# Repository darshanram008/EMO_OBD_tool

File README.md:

# On board diagnostic tool: developed for EMO energy pvt ltd. 
## On Board diagnostic tool is a simple PCB that can be interfaced with the internal battery management system that cannot be accessed during the maintence or diagnostics of the battery pack 

<!--Table  of contents
- [section 1](#section-1)
- [section 2](#section-2)-->

*The priamry functionn of the OBD tool:*
1. Communicate via controller area network (CAN) protocol to the battery and
request the BMS to send necessary data.
2. Communicate via the Universal serial asynchronous RX-TX protocol to the GUI
and deliver the data in human readable from.

*The following operations are implemenetd*
1. Request real time data containing cell voltages, pack voltage, pack current,
temperatures, error and faults from the BMS and transmit to the USB via UART
in the form of strings appended with certain identifiers.
2. Request the configuration parameters from the BMS that was already uploaded
upon getting a command request from the GUI
3. Push the new configuration parameters to the BMS on command request from the
GUI.
4. Request SD card data to be downloaded on request from the GUI.
5. Change baud rates of UART and CAN upon command request from GUI
6. Flow control between OBD and BMS whenever there is an event of exchanging
data.

## 
- Microcontroller unit: Microchip PIC18F27Q84
- CAN transciever: Microchip MCP2551; variable Baud rate upto 1Mbps
- UART to USB converter: Silicon labs CP2102; variable baud rate uptp 115200
- Micrchip MPLAB X IDE

<!-- > some block quote itseems -->

<!-- `this is where code comes` -->

----------------
<!--
[We can post any link if you want] (https://github.com/darshanram008/EMO_OBD_tool/edit/main/README.md)

This is a footnote, you press this it will take you to the footnote. [^1]
Note: Footnotes are always at the end of this file.
## SECTION 1
> This is table

|   Left side     | Right side     |
|-------------|------------|
| 1. The advantage is good | 1. The advantage is bad |
| 2. The advantage is good | 2. The advantage is bad |
| 3. The advantage is good | 3. The advantage is bad |
| 4. The advantage is good | 4. The advantage is bad |

```
{
   \\This is fenced code 
  if (count == 0)
  {
  printf("Hello, zeros"):  
  }

}
```
## SECTION 2
> Definitions

UART
: Universal Asyncronous receiver and transmitter

CAN
: Controller area network

~~Strikeout anything~~

- [x] Task completed
- [x] Task completed
- [ ] Task Incomplete
- [ ] Task incomplete

There are emoji as well! :joy:

i have more :angry:

take more 📶

==Some very important points==.

to put subscript you can do this H<sub>2</sub>O

To put superscript do this X<sup>2</sup>Y

[^1]: This is the footnote, you can add any references you want.

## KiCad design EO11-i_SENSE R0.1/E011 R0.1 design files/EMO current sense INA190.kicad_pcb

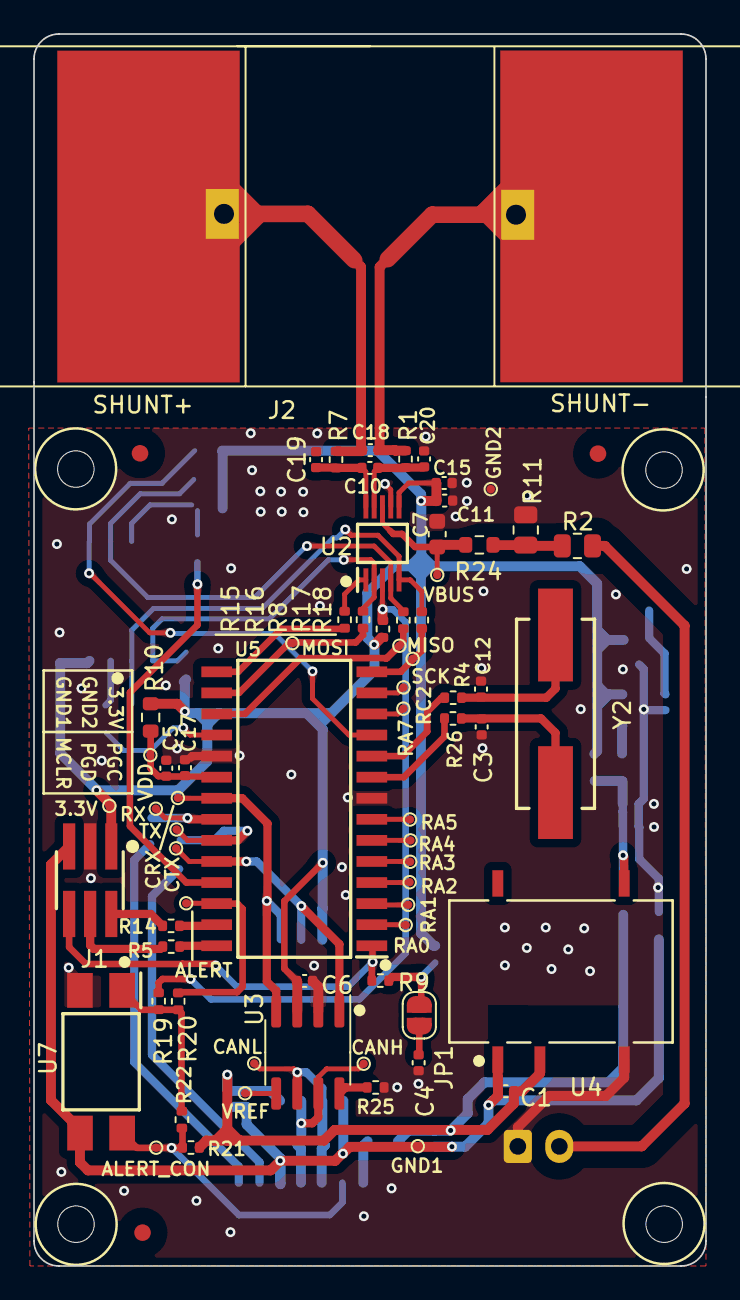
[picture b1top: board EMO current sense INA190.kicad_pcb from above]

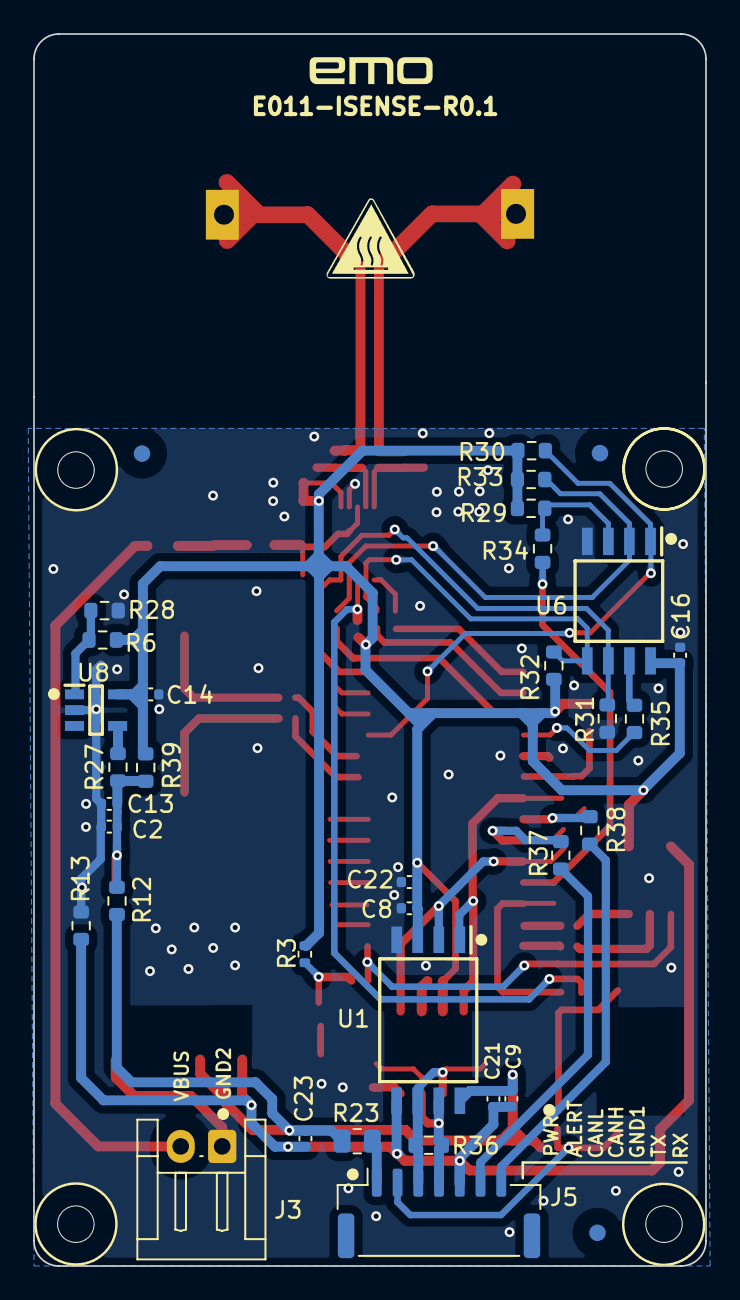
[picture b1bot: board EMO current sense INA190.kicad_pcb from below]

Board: 2 copper layers, 40.5 x 74.2 mm, 111 parts (35 on the bottom side), 62 nets.

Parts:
5V_PIC1: 3.3V; testpoint_0.5mm
C1, C4: 4.7uF; C_0402_1005Metric
C2: 10uF; C_0402_1005Metric
C3, C12: 33pF; C_0402_1005Metric
C5, C11: 100nF; C_0402_1005Metric
C6, C8, C9, C13, C16: 0.1uF; C_0402_1005Metric
C7: 100nF; C_0603_1608Metric
C10, C18, C19, C20, C21, C22: 1uF; C_0402_1005Metric
C14: 0.47uF; C_0402_1005Metric
C15, C17: 0.1nF; C_0402_1005Metric
C23: 47uF; C_0402_1005Metric
FID1, FID2, FID3, FID4, FID5, FID6: Fiducial; fiducial
H1, H2, H3, H4: MountingHole; MountingHole_2.2mm_M2
J1: samtec_03x02; SAMTEC_1.27mm_03x02
J2: current shunt; wsbs8518_shunt
J3: VBUS; JST_EH_S2B-EH_1x02_P2.50mm_Horizontal
J5: Conn_01x07_Pin; JST_GH_SM07B-GHS-TB_1x07-1MP_P1.25mm_Horizontal
JP1: Jumper_Open; SolderJumper-2_P1.3mm_Open_RoundedPad1.0x1.5mm
R1, R5, R7, R14, R25: 10R; R_0402_1005Metric
R2: 10k; R_0805_2012Metric
R3, R8: 10k; R_0402_1005Metric
R4, R15, R16, R17, R18, R19, R20, R21, R22, R26: 1k; R_0402_1005Metric
R6: 18k; R_0603_1608Metric
R9: 470R; R_0402_1005Metric
R10, R12, R13, R27, R37, R38, R39: 0R; R_0603_1608Metric
R11: 1k; R_0805_2012Metric
R23: 0R; R_0805_2012Metric
R24, R29, R30, R31, R32, R33, R34, R35: 1k; R_0603_1608Metric
R28: 10k; R_0603_1608Metric
R36: 120R; R_0603_1608Metric
TP1: ALERT_CON; testpoint_0.5mm
TP2: VBUS; testpoint_0.5mm
TP3: GND1; testpoint_0.5mm
TP4: CANH; testpoint_0.5mm
TP5: CANL; testpoint_0.5mm
TP6: MISO; testpoint_0.5mm
TP7: SCK; testpoint_0.5mm
TP8: MOSI; testpoint_0.5mm
TP9: GND2; testpoint_0.5mm
TP10: RA7; testpoint_0.5mm
TP11: RC2; testpoint_0.5mm
TP13: RA0; testpoint_0.5mm
TP14: RA1; testpoint_0.5mm
TP15: RA2; testpoint_0.5mm
TP16: RA3; testpoint_0.5mm
TP17: RA4; testpoint_0.5mm
TP18: RA5; testpoint_0.5mm
TP20: TX; testpoint_0.5mm
TP21: RX; testpoint_0.5mm
TP22: CRX; testpoint_0.5mm
TP23: CTX; testpoint_0.5mm
TP24: VDD; testpoint_0.5mm
TP25: ALERT; testpoint_0.5mm
TP27: VREF; testpoint_0.5mm
U1: MAX14878; MAX14878_SOIC127P1031X265-8N
U2: INA239; INA239_SOP50P490X110-10N
U3: SN65HVD230; SOIC-8_3.9x4.9mm_P1.27mm
U4: B0303XT-1WX2; B0303_B_XT-1WR2_MNS
U5: PIC18F27Q84; PIC18F27Q84_SOIC127P1030X265-28N
U6: W25Q32JVSS; W25Q32_SOIC127P790X216-8N
U7: PC817X3NIP1B; PC817X3_SOP254P960X420-4N
U8: ST715MR; ST715MR_SOT95P280X145-5N
Y2: 10MHz; ABLS8000MHZB4T

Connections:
+3.3V: 5V_PIC1.1, C6.2, C8.1, C11.2, C14.2, C15.2, C16.1, C22.2, J1.01, R3.1, R6.1, R8.1, R10.1, R27.2, R29.2, R30.2, R32.2, R33.2, U1.3 (VDDA), U2.6 (VS), U3.3 (VCC), U6.8 (VCC), U8.5 (OUT)
ALERT: R8.2, R19.1, U2.3 (ALERT)
ALERT_CON: J5.2, R21.1, R22.1, TP1.1, U7.4 (COLLECTOR)
ALERT_MCU: R20.2, TP25.1, U5.26 (RB5)
CANH: J5.4, R36.2, TP4.1, U1.7 (CANH), U3.7 (CANH)
CANL: J5.3, R36.1, TP5.1, U1.6 (CANL), U3.6 (CANL)
CANRX: TP22.1, U1.1 (RXD), U3.4 (R), U5.21 (RB0)
CANTX: TP23.1, U1.2 (TXD), U3.1 (D), U5.24 (RB3)
CLKIN: R26.1, U5.9 (RA7)
CLKOUT: R4.1, U5.10 (RA6)
CS_FLASH: R30.1, U5.11 (RC0), U6.1 (~CS)
CS_INA: R15.1, U2.1 (CS)
GND1: C1.2, C9.2, C21.2, C23.2, J1.05, J5.5, R13.2, TP3.1, U1.5 (GNDB), U4.1 (GND), U7.3 (EMITTER)
GND2: C2.2, C3.2, C4.2, C5.1, C6.1, C7.2, C8.2, C11.1, C12.2, C13.2, C14.1, C15.1, C16.2, C17.1, C19.2, C20.1, C22.1, J1.03, J3.1, R11.1, R13.1, R25.1, R28.2, R31.1, TP9.1, U1.4 (GNDA), U2.7 (GND), U3.2 (GND), U4.4 (0V), U5.8 (Vss), U5.19 (Vss), U6.4 (GND), U7.2 (CATHODE), U8.2 (GND)
HOLD: R35.2, U5.18 (RC7)
ICSDAT: R5.1, U5.28 (ICSPDAT/RB7)
ICSPLK: R14.1, U5.27 (ICSPCLK/RB6)
MCLR: J1.06, R9.2, U5.1 (VPP/MCLR/RE3)
MISO: R17.1, R33.1, U2.4 (MISO), U6.2 (DO(IO1))
MOSI: R16.1, R32.1, U2.2 (MOSI), U6.5 (DI(IO0))
unnamed: C3.1, R26.2, Y2.1
unnamed: C12.1, R4.2, Y2.2
unnamed: J1.02, R14.2
unnamed: J1.04, R5.2
unnamed: C18.1, J2.1, R1.1
unnamed: C18.2, J2.2, R7.1
unnamed: C4.1, JP1.1 (A)
unnamed: JP1.2 (B), R3.2, R9.1
unnamed: R2.1, R11.2, R24.1
unnamed: C10.2, C19.1, R7.2, U2.10 (IN+)
unnamed: C10.1, C20.2, R1.2, U2.9 (IN-)
unnamed: C7.1, R24.2, TP2.1, U2.8 (VBUS)
unnamed: R25.2, U3.8 (Rs)
unnamed: TP27.1, U3.5 (Vref)
unnamed: C2.1, C13.1, R12.1, R27.1, R39.2, U4.5 (+Vo)
unnamed: TP13.1, U5.2 (RA0)
unnamed: TP14.1, U5.3 (RA1)
unnamed: TP15.1, U5.4 (RA2)
unnamed: TP16.1, U5.5 (RA3)
unnamed: TP17.1, U5.6 (RA4)
unnamed: TP18.1, U5.7 (RA5)
unnamed: R38.1, TP21.1, U5.22 (RB1)
unnamed: R37.1, TP20.1, U5.23 (RB2)
unnamed: TP10.1, U5.12 (RC1)
unnamed: TP11.1, U5.13 (RC2)
unnamed: R18.2, TP7.1, U5.14 (RC3)
unnamed: R15.2, U5.15 (RC4)
unnamed: R16.2, TP8.1, U5.16 (RC5)
unnamed: R17.2, TP6.1, U5.17 (RC6)
unnamed: C5.2, C17.2, R10.2, TP24.1, U5.20 (VDD)
unnamed: R29.1, R34.1, U6.3 (IO2/WP(L))
unnamed: R35.1, U6.7 (IO3/HOLD(L))
unnamed: R19.2, R20.1, R22.2, U7.1 (ANODE)
unnamed: R6.2, R28.1, U8.1 (FB/NC)
unnamed: R39.1, U8.4 (IN)
PWR: J5.1, R23.2
RX: J5.7, R38.2
SCLK: R18.1, R31.2, U2.5 (SCLK), U6.6 (CLK)
TX: J5.6, R37.2
VBUS: J3.2, R2.2
VCC: C1.1, C9.1, C21.1, C23.1, R12.2, R21.2, R23.1, U1.8 (VDDB), U4.2 (Vin)
WP: R34.2, U5.25 (RB4)

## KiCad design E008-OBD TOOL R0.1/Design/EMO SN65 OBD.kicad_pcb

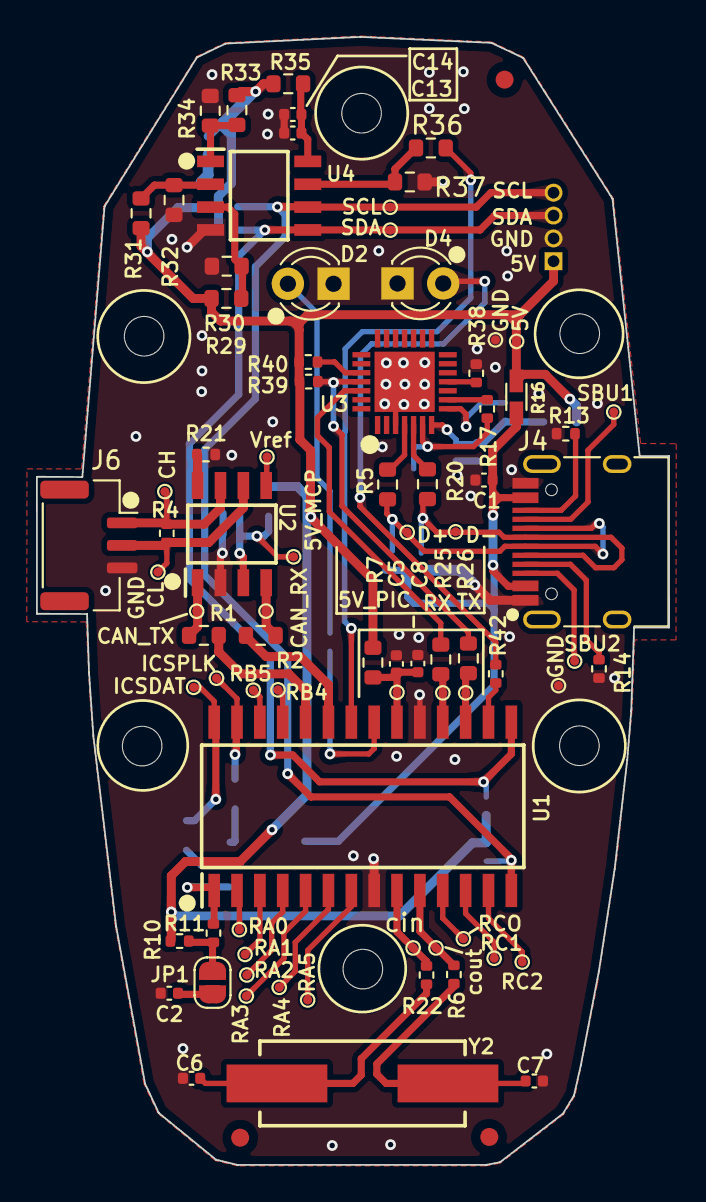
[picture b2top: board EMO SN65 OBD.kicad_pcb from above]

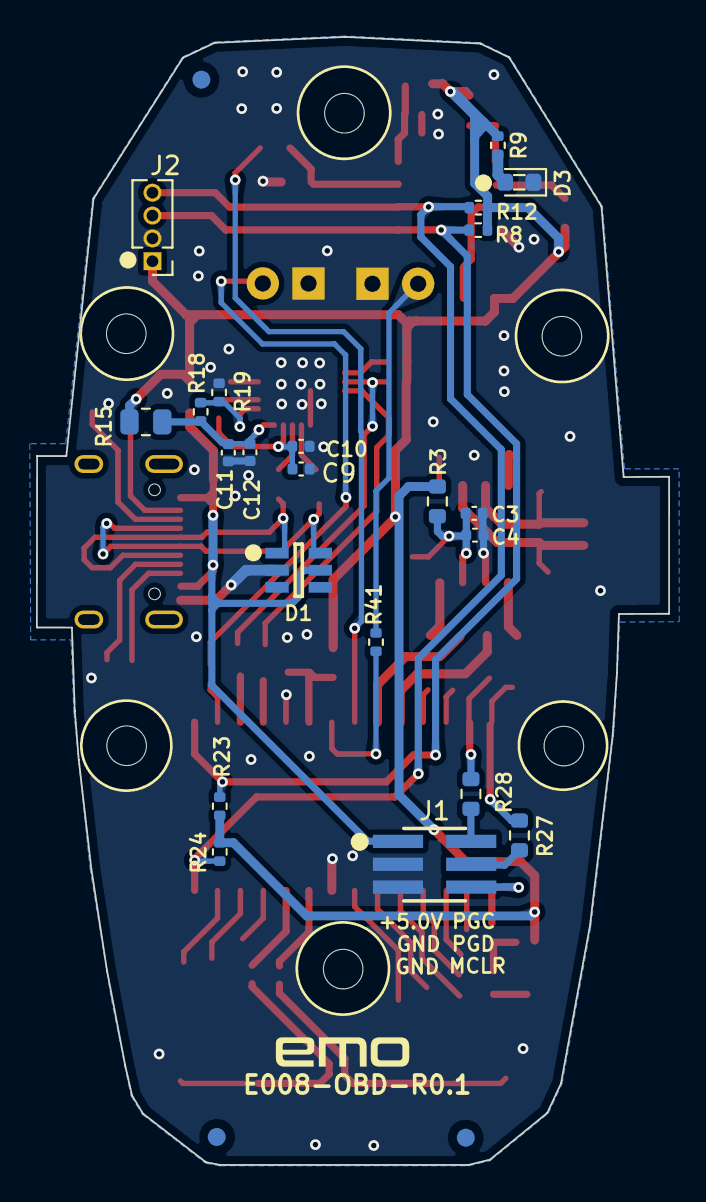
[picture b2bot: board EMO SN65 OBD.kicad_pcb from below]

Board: 2 copper layers, 35.1 x 62.7 mm, 109 parts (22 on the bottom side), 66 nets.

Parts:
C1, C2, C3, C9, C12: 4.7uF/25V; C_0402_1005Metric
C4: 1uF/25V; C_0402_1005Metric
C5: 0.1n/25V; C_0402_1005Metric
C6, C7: 33p/25V; C_0402_1005Metric
C8, C10, C11: 0.1uF/25V; C_0402_1005Metric
C13: 0.001uF/25V; C_0402_1005Metric
C14: 0.01uF/25V; C_0402_1005Metric
D1: SP0505BAHT; SP0505BAHT_SOT95P280X145-6N.kicad_mod
D2, D4: LED; LED_D3.0mm_IRBlack
D3: LED; LED_0603_1608Metric
H1, H2, H3, H4, H5, H6: MountingHole; MountingHole_2.2mm_M2
J1: samtec_03x02; SAMTEC_1.27mm_03x02
J2: I2C; PinHeader_1x04_P1.27mm_Vertical
J4: USB C 2.0; USB_C_Receptacle_HRO_TYPE-C-31-M-12
J6: CAN; JST_GH_SM03B-GHS-TB_1x03-1MP_P1.25mm_Horizontal
JP1: Jumper_2_Open; SolderJumper-2_P1.3mm_Open_RoundedPad1.0x1.5mm
R1, R2, R3, R5, R7, R20, R25, R26, R35: 0R; R_0603_1608Metric
R4: 120R; R_0402_1005Metric
R6, R8, R12, R17, R22, R23, R24: 1k; R_0402_1005Metric
R9, R41, R42: 330R; R_0402_1005Metric
R10: 10k; R_0402_1005Metric
R11: 470R; R_0402_1005Metric
R13, R14: 5.1k; R_0402_1005Metric
R15: 0R; R_0805_2012Metric
R16: 5A fuse; FUSE
R18: 22.1k; R_0402_1005Metric
R19: 47.5k; R_0402_1005Metric
R21, R38, R39, R40: 10K; R_0402_1005Metric
R27, R28: 10R; R_0603_1608Metric
R29, R30, R31, R32, R33, R34, R36, R37: 1k; R_0603_1608Metric
SBU2: SBU2; testpoint_0.5mm
TP1: RA0; testpoint_0.5mm
TP2: RA1; testpoint_0.5mm
TP3: RA2; testpoint_0.5mm
TP4: RA3; testpoint_0.5mm
TP5: RA4; testpoint_0.5mm
TP6: RA5; testpoint_0.5mm
TP7: D-; testpoint_0.5mm
TP8: RC1; testpoint_0.5mm
TP9: RC2; testpoint_0.5mm
TP10: RB5; testpoint_0.5mm
TP11: 5V; testpoint_0.5mm
TP12: RB4; testpoint_0.5mm
TP15: ICSPLK; testpoint_0.5mm
TP16: ICSDAT; testpoint_0.5mm
TP17: SDA; testpoint_0.5mm
TP18: SCL; testpoint_0.5mm
TP19: SBU1; testpoint_0.5mm
TP20, TP33: GND; testpoint_0.5mm
TP21: CH; testpoint_0.5mm
TP22: CL; testpoint_0.5mm
TP23: CAN_TX; testpoint_0.5mm
TP24: CAN_RX; testpoint_0.5mm
TP25: 5V_PIC; testpoint_0.5mm
TP26: cout; testpoint_0.5mm
TP27: cin; testpoint_0.5mm
TP29: 5V_MCP; testpoint_0.5mm
TP30: Vref; testpoint_0.5mm
TP31: RCO; testpoint_0.5mm
TP32: D+; testpoint_0.5mm
TP38: TX; testpoint_0.5mm
TP39: RX; testpoint_0.5mm
U1: PIC18F27Q84; PIC18F27Q84_SOIC127P1030X265-28N
U2: MCP2551-I-P; SOIC127P600X175-8N
U3: CP2102-GMR; QFN50P500X500X100-29N-D
U4: AT24C256C-SSHL-T; AT24C256_SOIC127P600X175-8N
Y2: 10MHz; ABLS8000MHZB4T

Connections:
5V: J2.1, R3.1, R7.1, R8.2, R9.1, R10.1, R12.2, R15.2, R16.1, R23.2, R24.2, R29.2, R31.2, R33.2, R35.1, R39.2, R40.2, TP11.1
+5.0V: C1.1, D1.5 (L4), J1.01, J4.A4 (VBUS), J4.A9 (VBUS), J4.B4 (VBUS), J4.B9 (VBUS), R16.2
CAN_RX: R2.2, U1.23 (RB2)
CAN_TX: R1.2, U1.24 (RB3)
CLKIN: R22.1, TP27.1, U1.9 (RA7)
CLKOUT: R6.1, TP26.1, U1.10 (RA6)
D+: D1.6 (L5), J4.A6 (DP1), J4.B6 (DP2), R5.2, TP32.1
D-: D1.1 (L1), J4.A7 (DN1), J4.B7 (DN2), R20.2, TP7.1
GND: C1.2, C2.2, C3.2, C4.2, C5.1, C6.2, C7.2, C8.1, C9.2, C10.1, C11.1, C12.1, C13.2, C14.2, D1.2 (VN), D2.1 (K), D3.1 (K), D4.1 (K), J1.03, J1.05, J2.2, J4.A1 (GND), J4.A12 (GND), J4.B1 (GND), J4.B12 (GND), J6.3, R13.2, R14.2, R19.2, R21.2, R30.1, R32.1, R34.1, R37.1, R38.2, TP20.1, TP33.1, U1.8 (Vss), U1.19 (Vss), U2.2 (VSS), U3.3 (GND), U3.29 (TPAD), U4.4 (GND)
ICSDAT: R27.1, TP16.1, U1.28 (ICSPDAT/RB7)
ICSPLK: R28.1, TP15.1, U1.27 (ICSPCLK/RB6)
MCLR: J1.06, R11.2, U1.1 (VPP/MCLR/RE3)
unnamed: C6.1, R22.2, Y2.1
unnamed: C7.1, R6.2, Y2.2
unnamed: D2.2 (A), R41.2
unnamed: D3.2 (A), R9.2
unnamed: D4.2 (A), R42.2
unnamed: J1.02, R28.2
unnamed: J1.04, R27.2
unnamed: J4.A5 (CC1), R14.1
unnamed: J4.B5 (CC2), R13.1
unnamed: J4.A8 (SBU1), TP19.1
unnamed: J4.B8 (SBU2), SBU2.1
unnamed: J6.1, R4.1, TP21.1, U2.7 (CANH)
unnamed: J6.2, R4.2, TP22.1, U2.6 (CANL)
unnamed: C2.1, JP1.1 (A)
unnamed: JP1.2 (B), R10.2, R11.1
unnamed: TP1.1, U1.2 (RA0)
unnamed: TP2.1, U1.3 (RA1)
unnamed: TP3.1, U1.4 (RA2)
unnamed: TP4.1, U1.5 (RA3)
unnamed: TP5.1, U1.6 (RA4)
unnamed: TP6.1, U1.7 (RA5)
unnamed: R41.1, U1.21 (RB0)
unnamed: TP12.1, U1.25 (RB4)
unnamed: TP10.1, U1.26 (RB5)
unnamed: TP31.1, U1.11 (RC0)
unnamed: TP8.1, U1.12 (RC1)
unnamed: TP9.1, U1.13 (RC2)
unnamed: R42.1, U1.16 (RC5)
unnamed: C5.2, C8.2, R7.2, TP25.1, U1.20 (VDD)
unnamed: R2.1, TP24.1, U2.4 (RXD)
unnamed: R21.1, U2.8 (Rs)
unnamed: R1.1, TP23.1, U2.1 (TXD)
unnamed: C3.1, C4.1, R3.2, TP29.1, U2.3 (VDD)
unnamed: TP30.1, U2.5 (Vref)
unnamed: R5.1, U3.4 (D+)
unnamed: R20.1, U3.5 (D-)
unnamed: C11.2, C12.2, R15.1, R18.1, U3.7 (REGIN)
unnamed: R40.1, U3.24 (RTS)
unnamed: R26.2, R39.1, U3.25 (RXD)
unnamed: R25.2, U3.26 (TXD)
unnamed: R18.2, R19.1, U3.8 (VBUS)
unnamed: C9.1, C10.2, R17.1, U3.6 (VDD)
unnamed: R17.2, U3.9 (~RST)
unnamed: R38.1, U3.11 (~SUSPEND)
unnamed: R33.1, R34.2, U4.1 (A0)
unnamed: R31.1, R32.2, U4.2 (A1)
unnamed: R29.1, R30.2, U4.3 (A2)
unnamed: C13.1, C14.1, R35.2, U4.8 (VCC)
unnamed: R36.2, R37.2, U4.7 (WP)
SCL: J2.4, R12.1, R24.1, TP18.1, U1.14 (RC3), U4.6 (SCL)
SDA: J2.3, R8.1, R23.1, TP17.1, U1.15 (RC4), U4.5 (SDA)
UART_RX: R25.1, TP39.1, U1.18 (RC7)
UART_TX: R26.1, TP38.1, U1.17 (RC6)
WP: R36.1, U1.22 (RB1)

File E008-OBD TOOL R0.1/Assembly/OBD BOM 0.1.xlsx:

Sl.No | Reference | Value | Footprint | Description | MPN | Manufacturer | Qty
1 | C1-C3, C9, C12 | 4.7uF/25V | Capacitor_SMD:C_0402_1005Metric | 402 | CC0402MRX5R7BB475 | YAGEO | 5
2 | C4 | 1uF/25V | Capacitor_SMD:C_0402_1005Metric | 402 | CC0402KPX5R7BB105 | YAGEO | 1
3 | C5 | 0.1n/25V | Capacitor_SMD:C_0402_1005Metric | 402 | CC0402KRX7R7BB101 | YAGEO | 1
4 | C6, C7 | 33p/25V | Capacitor_SMD:C_0402_1005Metric | 402 | CC0201JPNPO7BN330 | YAGEO | 2
5 | C8, C10, C11 | 0.1uF/25V | Capacitor_SMD:C_0402_1005Metric | 402 | CC0402KRX7R7BB104 | YAGEO | 3
6 | C13 | 0.001uF/25V | Capacitor_SMD:C_0402_1005Metric | 402 | CC0100KRX7R7BB102 | YAGEO | 1
7 | C14 | 0.01uF/25V | Capacitor_SMD:C_0402_1005Metric | 402 | CC0805JKNPO7BN103 | YAGEO | 1
8 | D1 | SP0505BAHT | Custommm:SP0505BAHT_SOT95P280X145-6N.kicad_mod |  | SP0505BAHTG |  | 1
9 | D2, D4 | LED | LED_THT:LED_D3.0mm_IRBlack | LED |  | bivar | 2
10 | D3 | LED | LED_SMD:LED_0603_1608Metric | LED |  | bivar | 1
11 | H1-H6 | MountingHole | MountingHole:MountingHole_2.2mm_M2 |  |  |  | 6
12 | J1 | samtec_03x02 | Custommm:SAMTEC_1.27mm_03x02 | DEBUG |  |  | 1
13 | J2 | I2C | Connector_PinHeader_1.27mm:PinHeader_1x04_P1.27mm_Vertical | 4 pin JST connector | 240-004 | Digilent | 1
14 | J4 | USB C 2.0 | Connector_USB:USB_C_Receptacle_HRO_TYPE-C-31-M-12 | USB C | USB4105-GF-A | GCT | 1
15 | J6 | CAN | Connector_JST:JST_GH_SM03B-GHS-TB_1x03-1MP_P1.25mm_Horizontal |  | SM03B-GHS-TB |  | 1
16 | JP1 | Jumper_2_Open | Jumper:SolderJumper-2_P1.3mm_Open_RoundedPad1.0x1.5mm |  |  |  | 1
17 | R1-R3, R5, R7, R20, R25, R26, R35 | 0R | Resistor_SMD:R_0603_1608Metric | 603 | RC0603FR-SNE96L | YAGEO | 9
18 | R4 | 120R | Resistor_SMD:R_0402_1005Metric | 402 | RC0402FR-07120RL | YAGEO | 1
19 | R6, R8, R12, R17, R22-R24 | 1k | Resistor_SMD:R_0402_1005Metric | 402 | RT0402BRE071KL | YAGEO | 7
20 | R9, R41, R42 | 330R | Resistor_SMD:R_0402_1005Metric | 402 | RC0402JR-7D330RL | YAGEO | 3
21 | R10 | 10k | Resistor_SMD:R_0402_1005Metric | 402 | RC0402FR-0710KL | YAGEO | 1
22 | R11 | 470R | Resistor_SMD:R_0402_1005Metric | 402 | RC0402FR-07470RL | YAGEO | 1
23 | R13, R14 | 5.1k | Resistor_SMD:R_0402_1005Metric | 402 | RC0402FR-075K1L | YAGEO | 2
24 | R15 | 0R | Resistor_SMD:R_0805_2012Metric | 603 | RC0603FR-SNE96L | YAGEO | 1
25 | R16 | 5A fuse | Custommm:FUSE | - | 0494.250NR | YAGEO | 1
26 | R18 | 22.1k | Resistor_SMD:R_0402_1005Metric | 402 | RC0402FR-1322K1L | YAGEO | 1
27 | R19 | 47.5k | Resistor_SMD:R_0402_1005Metric | 402 | RC0402FR-0747K5L | YAGEO | 1
28 | R21, R38-R40 | 10K | Resistor_SMD:R_0402_1005Metric | 402 | RC0402FR-0710KL | YAGEO | 4
29 | R27, R28 | 10R | Resistor_SMD:R_0603_1608Metric | 603 | RC0603FR-0710RL | YAGEO | 2
30 | R29-R34, R36, R37 | 1k | Resistor_SMD:R_0603_1608Metric | 603 | RT0603WRE071KL | YAGEO | 8
31 | U1 | PIC18F27Q84 | Custommm:PIC18F27Q84_SOIC127P1030X265-28N | MCU | PIC18F27Q84-E/SO | Microchip Technology | 1
32 | U2 | MCP2551-I-P | mcp2551:SOIC127P600X175-8N | CAN IC | MCP2551-I/SN | Microchip Technology | 1
33 | U3 | CP2102-GMR | Custommm:QFN50P500X500X100-29N-D | UART to USB | 634-CP2102-GMR |  | 1
34 | U4 | AT24C256C-SSHL-T | Custommm:AT24C256_SOIC127P600X175-8N | EEPROM | AT24C256C-SSHL-T |  | 1
35 | Y2 | 10MHz | Custommm:ABLS8000MHZB4T | CRYSTAL | ABM7-10.000MHZ-D2Y-T | ABRACON | 1

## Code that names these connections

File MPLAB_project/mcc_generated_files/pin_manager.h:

/**
  @Generated Pin Manager Header File

  @Company:
    Microchip Technology Inc.

  @File Name:
    pin_manager.h

  @Summary:
    This is the Pin Manager file generated using PIC10 / PIC12 / PIC16 / PIC18 MCUs

  @Description
    This header file provides APIs for driver for .
    Generation Information :
        Product Revision  :  PIC10 / PIC12 / PIC16 / PIC18 MCUs - 1.81.8
        Device            :  PIC18F27Q84
        Driver Version    :  2.11
    The generated drivers are tested against the following:
        Compiler          :  XC8 2.36 and above
        MPLAB 	          :  MPLAB X 6.00	
*/

/*
    (c) 2018 Microchip Technology Inc. and its subsidiaries. 
    
    Subject to your compliance with these terms, you may use Microchip software and any 
    derivatives exclusively with Microchip products. It is your responsibility to comply with third party 
    license terms applicable to your use of third party software (including open source software) that 
    may accompany Microchip software.
    
    THIS SOFTWARE IS SUPPLIED BY MICROCHIP "AS IS". NO WARRANTIES, WHETHER 
    EXPRESS, IMPLIED OR STATUTORY, APPLY TO THIS SOFTWARE, INCLUDING ANY 
    IMPLIED WARRANTIES OF NON-INFRINGEMENT, MERCHANTABILITY, AND FITNESS 
    FOR A PARTICULAR PURPOSE.
    
    IN NO EVENT WILL MICROCHIP BE LIABLE FOR ANY INDIRECT, SPECIAL, PUNITIVE, 
    INCIDENTAL OR CONSEQUENTIAL LOSS, DAMAGE, COST OR EXPENSE OF ANY KIND 
    WHATSOEVER RELATED TO THE SOFTWARE, HOWEVER CAUSED, EVEN IF MICROCHIP 
    HAS BEEN ADVISED OF THE POSSIBILITY OR THE DAMAGES ARE FORESEEABLE. TO 
    THE FULLEST EXTENT ALLOWED BY LAW, MICROCHIP'S TOTAL LIABILITY ON ALL 
    CLAIMS IN ANY WAY RELATED TO THIS SOFTWARE WILL NOT EXCEED THE AMOUNT 
    OF FEES, IF ANY, THAT YOU HAVE PAID DIRECTLY TO MICROCHIP FOR THIS 
    SOFTWARE.
*/

#ifndef PIN_MANAGER_H
#define PIN_MANAGER_H

/**
  Section: Included Files
*/

#include <xc.h>

#define INPUT   1
#define OUTPUT  0

#define HIGH    1
#define LOW     0

#define ANALOG      1
#define DIGITAL     0

#define PULL_UP_ENABLED      1
#define PULL_UP_DISABLED     0

// get/set IO_RB0 aliases
#define IO_RB0_TRIS                 TRISBbits.TRISB0
#define IO_RB0_LAT                  LATBbits.LATB0
#define IO_RB0_PORT                 PORTBbits.RB0
#define IO_RB0_WPU                  WPUBbits.WPUB0
#define IO_RB0_OD                   ODCONBbits.ODCB0
#define IO_RB0_ANS                  ANSELBbits.ANSELB0
#define IO_RB0_SetHigh()            do { LATBbits.LATB0 = 1; } while(0)
#define IO_RB0_SetLow()             do { LATBbits.LATB0 = 0; } while(0)
#define IO_RB0_Toggle()             do { LATBbits.LATB0 = ~LATBbits.LATB0; } while(0)
#define IO_RB0_GetValue()           PORTBbits.RB0
#define IO_RB0_SetDigitalInput()    do { TRISBbits.TRISB0 = 1; } while(0)
#define IO_RB0_SetDigitalOutput()   do { TRISBbits.TRISB0 = 0; } while(0)
#define IO_RB0_SetPullup()          do { WPUBbits.WPUB0 = 1; } while(0)
#define IO_RB0_ResetPullup()        do { WPUBbits.WPUB0 = 0; } while(0)
#define IO_RB0_SetPushPull()        do { ODCONBbits.ODCB0 = 0; } while(0)
#define IO_RB0_SetOpenDrain()       do { ODCONBbits.ODCB0 = 1; } while(0)
#define IO_RB0_SetAnalogMode()      do { ANSELBbits.ANSELB0 = 1; } while(0)
#define IO_RB0_SetDigitalMode()     do { ANSELBbits.ANSELB0 = 0; } while(0)

// get/set RB2 procedures
#define RB2_SetHigh()            do { LATBbits.LATB2 = 1; } while(0)
#define RB2_SetLow()             do { LATBbits.LATB2 = 0; } while(0)
#define RB2_Toggle()             do { LATBbits.LATB2 = ~LATBbits.LATB2; } while(0)
#define RB2_GetValue()              PORTBbits.RB2
#define RB2_SetDigitalInput()    do { TRISBbits.TRISB2 = 1; } while(0)
#define RB2_SetDigitalOutput()   do { TRISBbits.TRISB2 = 0; } while(0)
#define RB2_SetPullup()             do { WPUBbits.WPUB2 = 1; } while(0)
#define RB2_ResetPullup()           do { WPUBbits.WPUB2 = 0; } while(0)
#define RB2_SetAnalogMode()         do { ANSELBbits.ANSELB2 = 1; } while(0)
#define RB2_SetDigitalMode()        do { ANSELBbits.ANSELB2 = 0; } while(0)

// get/set RB3 procedures
#define RB3_SetHigh()            do { LATBbits.LATB3 = 1; } while(0)
#define RB3_SetLow()             do { LATBbits.LATB3 = 0; } while(0)
#define RB3_Toggle()             do { LATBbits.LATB3 = ~LATBbits.LATB3; } while(0)
#define RB3_GetValue()              PORTBbits.RB3
#define RB3_SetDigitalInput()    do { TRISBbits.TRISB3 = 1; } while(0)
#define RB3_SetDigitalOutput()   do { TRISBbits.TRISB3 = 0; } while(0)
#define RB3_SetPullup()             do { WPUBbits.WPUB3 = 1; } while(0)
#define RB3_ResetPullup()           do { WPUBbits.WPUB3 = 0; } while(0)
#define RB3_SetAnalogMode()         do { ANSELBbits.ANSELB3 = 1; } while(0)
#define RB3_SetDigitalMode()        do { ANSELBbits.ANSELB3 = 0; } while(0)

// get/set IO_RC5 aliases
#define IO_RC5_TRIS                 TRISCbits.TRISC5
#define IO_RC5_LAT                  LATCbits.LATC5
#define IO_RC5_PORT                 PORTCbits.RC5
#define IO_RC5_WPU                  WPUCbits.WPUC5
#define IO_RC5_OD                   ODCONCbits.ODCC5
#define IO_RC5_ANS                  ANSELCbits.ANSELC5
#define IO_RC5_SetHigh()            do { LATCbits.LATC5 = 1; } while(0)
#define IO_RC5_SetLow()             do { LATCbits.LATC5 = 0; } while(0)
#define IO_RC5_Toggle()             do { LATCbits.LATC5 = ~LATCbits.LATC5; } while(0)
#define IO_RC5_GetValue()           PORTCbits.RC5
#define IO_RC5_SetDigitalInput()    do { TRISCbits.TRISC5 = 1; } while(0)
#define IO_RC5_SetDigitalOutput()   do { TRISCbits.TRISC5 = 0; } while(0)
#define IO_RC5_SetPullup()          do { WPUCbits.WPUC5 = 1; } while(0)
#define IO_RC5_ResetPullup()        do { WPUCbits.WPUC5 = 0; } while(0)
#define IO_RC5_SetPushPull()        do { ODCONCbits.ODCC5 = 0; } while(0)
#define IO_RC5_SetOpenDrain()       do { ODCONCbits.ODCC5 = 1; } while(0)
#define IO_RC5_SetAnalogMode()      do { ANSELCbits.ANSELC5 = 1; } while(0)
#define IO_RC5_SetDigitalMode()     do { ANSELCbits.ANSELC5 = 0; } while(0)

// get/set RC6 procedures
#define RC6_SetHigh()            do { LATCbits.LATC6 = 1; } while(0)
#define RC6_SetLow()             do { LATCbits.LATC6 = 0; } while(0)
#define RC6_Toggle()             do { LATCbits.LATC6 = ~LATCbits.LATC6; } while(0)
#define RC6_GetValue()              PORTCbits.RC6
#define RC6_SetDigitalInput()    do { TRISCbits.TRISC6 = 1; } while(0)
#define RC6_SetDigitalOutput()   do { TRISCbits.TRISC6 = 0; } while(0)
#define RC6_SetPullup()             do { WPUCbits.WPUC6 = 1; } while(0)
#define RC6_ResetPullup()           do { WPUCbits.WPUC6 = 0; } while(0)
#define RC6_SetAnalogMode()         do { ANSELCbits.ANSELC6 = 1; } while(0)
#define RC6_SetDigitalMode()        do { ANSELCbits.ANSELC6 = 0; } while(0)

// get/set RC7 procedures
#define RC7_SetHigh()            do { LATCbits.LATC7 = 1; } while(0)
#define RC7_SetLow()             do { LATCbits.LATC7 = 0; } while(0)
#define RC7_Toggle()             do { LATCbits.LATC7 = ~LATCbits.LATC7; } while(0)
#define RC7_GetValue()              PORTCbits.RC7
#define RC7_SetDigitalInput()    do { TRISCbits.TRISC7 = 1; } while(0)
#define RC7_SetDigitalOutput()   do { TRISCbits.TRISC7 = 0; } while(0)
#define RC7_SetPullup()             do { WPUCbits.WPUC7 = 1; } while(0)
#define RC7_ResetPullup()           do { WPUCbits.WPUC7 = 0; } while(0)
#define RC7_SetAnalogMode()         do { ANSELCbits.ANSELC7 = 1; } while(0)
#define RC7_SetDigitalMode()        do { ANSELCbits.ANSELC7 = 0; } while(0)

/**
   @Param
    none
   @Returns
    none
   @Description
    GPIO and peripheral I/O initialization
   @Example
    PIN_MANAGER_Initialize();
 */
void PIN_MANAGER_Initialize (void);

/**
 * @Param
    none
 * @Returns
    none
 * @Description
    Interrupt on Change Handling routine
 * @Example
    PIN_MANAGER_IOC();
 */
void PIN_MANAGER_IOC(void);



#endif // PIN_MANAGER_H
/**
 End of File
*/

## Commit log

2024-04-03 Create s
2024-04-03 Update s
2026-01-10 Rename OBD_TOOL_PCB_FINAL.X.rar to MPLAB_OBD.X.rar
2026-01-11 Add copyright notice to LICENSE file
